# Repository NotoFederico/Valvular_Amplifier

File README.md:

# Valvular Amplifier for headphones

---

---

### Download
| Latest release | Latest development build |
|----------------|--------------------------|
|  |  |

---

# Contents
- 1 - [Introduction](#1-introduction)
- 2 - [Contributing](#4-contributing)
- 3 - [Licence](#5-licence)

---

# 1. Introduction

Personal project developed with KiCAD. In order to learn about valve technology and its uses in the world of audio.
The result was an audio amplifier that provides a much warmer and deeper sound to the user's ears.

---

# 2. Contributing

Pong Game uses the [gitflow workflow](https://www.atlassian.com/git/tutorials/comparing-workflows#gitflow-workflow). If you are implementing a new feature or logic from the original game, please branch off and perform pull requests to ```develop```. If you are fixing a bug for the next release, please branch off and perform pull requests to the correct release branch. ```master``` only contains tagged releases, you should never branch off this.

---

# 3. Licence
Valvular Amplifier is licensed under the GNU General Public License version 3.

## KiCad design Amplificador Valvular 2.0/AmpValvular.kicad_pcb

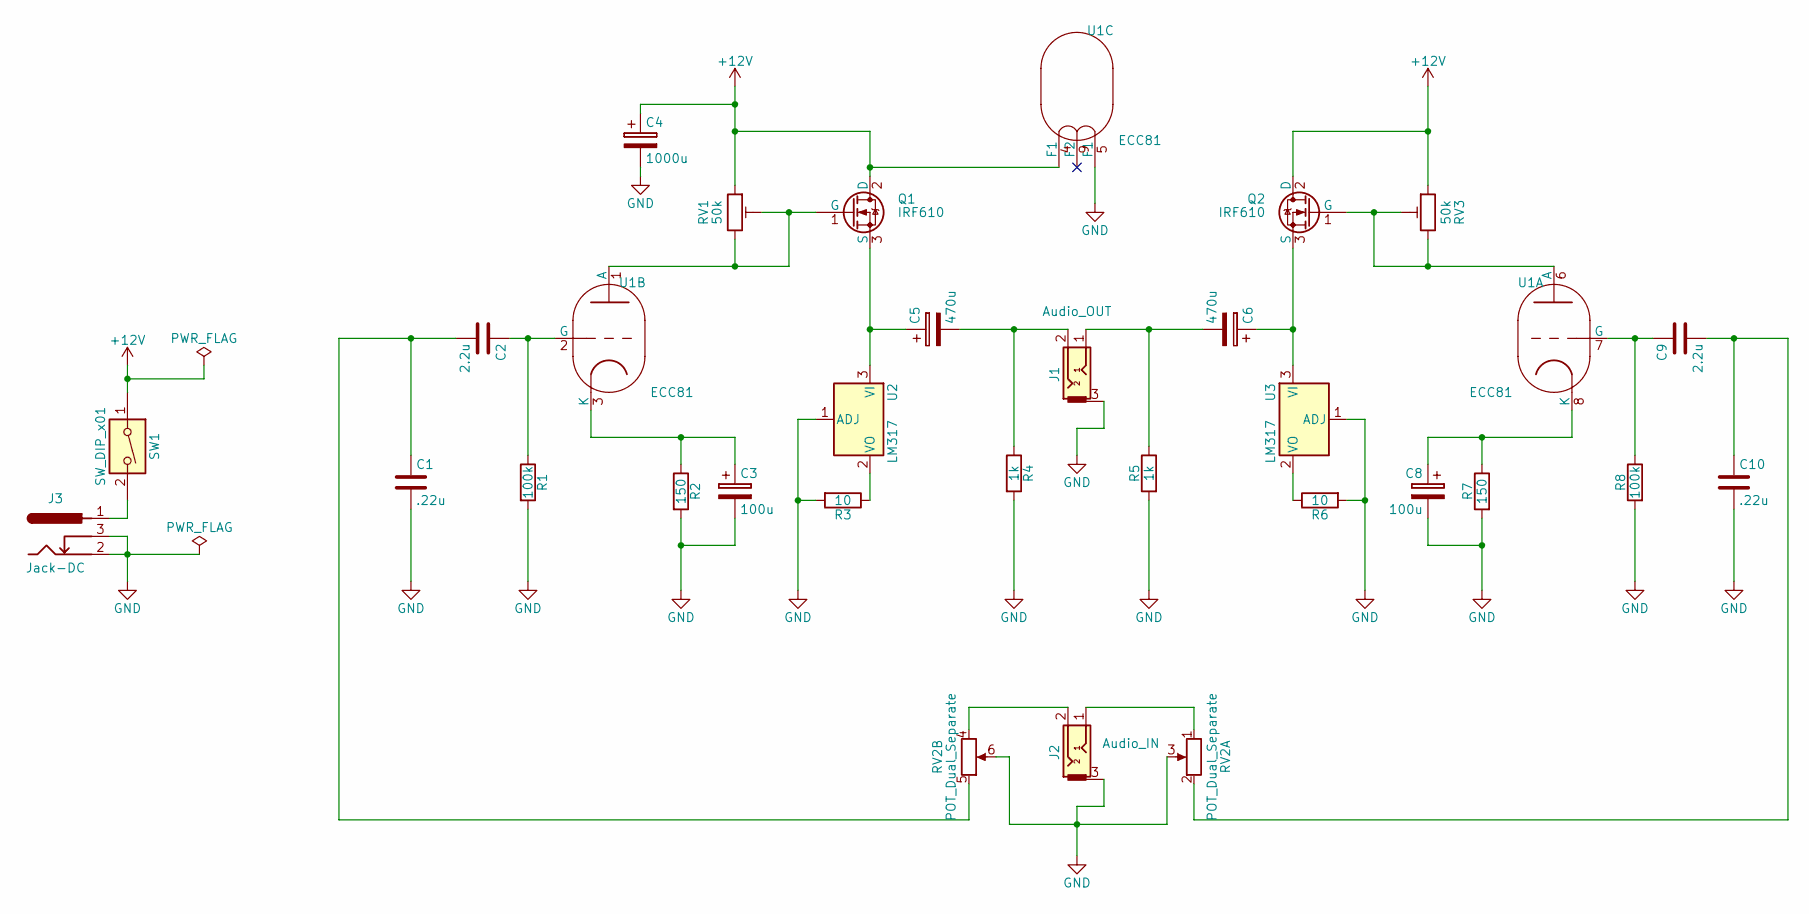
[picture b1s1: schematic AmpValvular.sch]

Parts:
C1, C10: .22u; C_Rect_L7.0mm_W3.5mm_P5.00mm
C2, C9: 2.2u; C_Rect_L18.0mm_W8.0mm_P15.00mm_FKS3_FKP3
C3, C8: 100u; CP_Radial_D5.0mm_P2.50mm
C4: 1000u; CP_Radial_D14.0mm_P5.00mm
C5, C6: 470u; CP_Radial_D8.0mm_P5.00mm
J1: Audio_OUT; Tayda_3.5mm_stereo_TRS_jack_A-853
J2: Audio_IN; Tayda_3.5mm_stereo_TRS_jack_A-853
J3: Jack-DC; JACK_ALIM
Q1, Q2: IRF610; TO-220-3_Vertical
R1, R8: 100k; R_Axial_DIN0207_L6.3mm_D2.5mm_P10.16mm_Horizontal
R2, R7: 150; R_Axial_DIN0207_L6.3mm_D2.5mm_P10.16mm_Horizontal
R3, R6: 10; R_Axial_DIN0309_L9.0mm_D3.2mm_P15.24mm_Horizontal
R4, R5: 1k; R_Axial_DIN0207_L6.3mm_D2.5mm_P10.16mm_Horizontal
RV1, RV3: 50k; Potentiometer_Trimmer_Bourns_3296W
RV2: POT_Dual_Separate; Potentiometer_Piher_PC-16_Double_Vertical
SW1: SW_DIP_x01; PhoenixContact_MSTBVA-G_02x5.00mm_Vertical
U1: ECC81; VALVE-NOVAL_P
U2, U3: LM317; TO-220-3_Vertical

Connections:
+12V: C4.1, Q1.2 (D), Q2.2 (D), RV1.1, RV3.1, SW1.1, U1.4 (F1)
GND: C1.2, C3.2, C4.2, C8.2, C10.2, J1.3, J2.3, J3.2, J3.3, R1.2, R2.2, R3.2, R4.2, R5.2, R6.2, R7.2, R8.2, RV2.3 (6), RV2.6, U1.5 (F1), U2.1 (ADJ), U3.1 (ADJ)
unnamed: C1.1, C2.2, RV2.5
unnamed: C2.1, R1.1, U1.2 (G)
unnamed: C3.1, R2.1, U1.3 (K)
unnamed: C5.1, Q1.3 (S), U2.3 (VI)
unnamed: C5.2, J1.2, R4.1
unnamed: C6.1, Q2.3 (S), U3.3 (VI)
unnamed: C6.2, J1.1, R5.1
unnamed: C8.1, R7.1, U1.8 (K)
unnamed: C9.1, R8.1, U1.7 (G)
unnamed: C9.2, C10.1, RV2.2 (5)
unnamed: J2.1, RV2.1 (4)
unnamed: J2.2, RV2.4
unnamed: J3.1, SW1.2
unnamed: Q1.1 (G), RV1.2, RV1.3, U1.1 (A)
unnamed: Q2.1 (G), RV3.2, RV3.3, U1.6 (A)
unnamed: R3.1, U2.2 (VO)
unnamed: R6.1, U3.2 (VO)

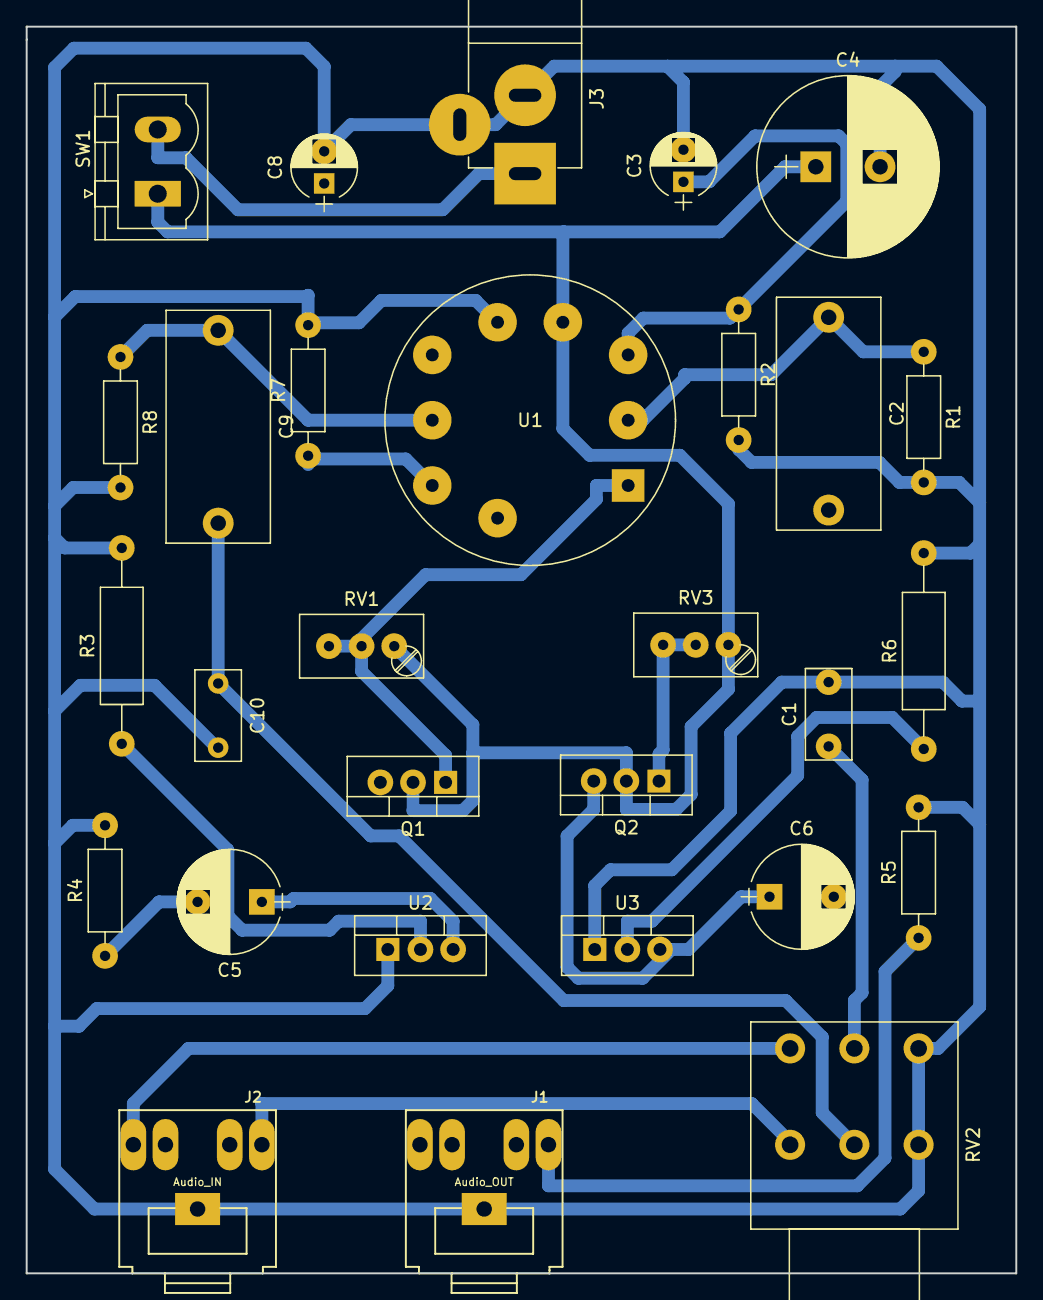
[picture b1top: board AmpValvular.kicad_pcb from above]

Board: 2 copper layers, 77.0 x 97.0 mm, 29 parts (0 on the bottom side), 19 nets.

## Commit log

2021-04-19 Create LICENSE
